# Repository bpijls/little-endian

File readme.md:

#Readme

Little-Endian is a little rover-like robot to be used for educational purposes, created by students from the Amsterdam University of Applied Sciences, (HBO-ICT, Minor IoT). The robot itself is based on a WiFi enabled microcontroller (the ESP8266) and can be programmed with a web-based blockly programming environment. For more detailed information, refer to the [design documentation](https://github.com/bpijls/little-endian/tree/master/documentation). 

**Building the robot**
The robot frame can be lasercut from 3mm mdf 
[PCB](https://dirtypcbs.com/store/designer/details/23296/6093/little-endian)

**Installation**

*	Install 'docker' and 'docker-compose' on your webserver
*	Clone this repository to a folder
*	Rename env.example to .env and determine the host name and virtual host subdomains
*	Run 'docker-compose build' from the root folder of this repository
*	To run the server, run 'docker-compose up' from the root folder
*	the server can be reached using the virtual host names you determined in the .env file or by typing the IP addres of the server in the address bar of your webbrowser. The webapplications runs on port 3000 and the socket server runs on port 8000.

**Usage**

Log in to the webapplication by entering a robot-id

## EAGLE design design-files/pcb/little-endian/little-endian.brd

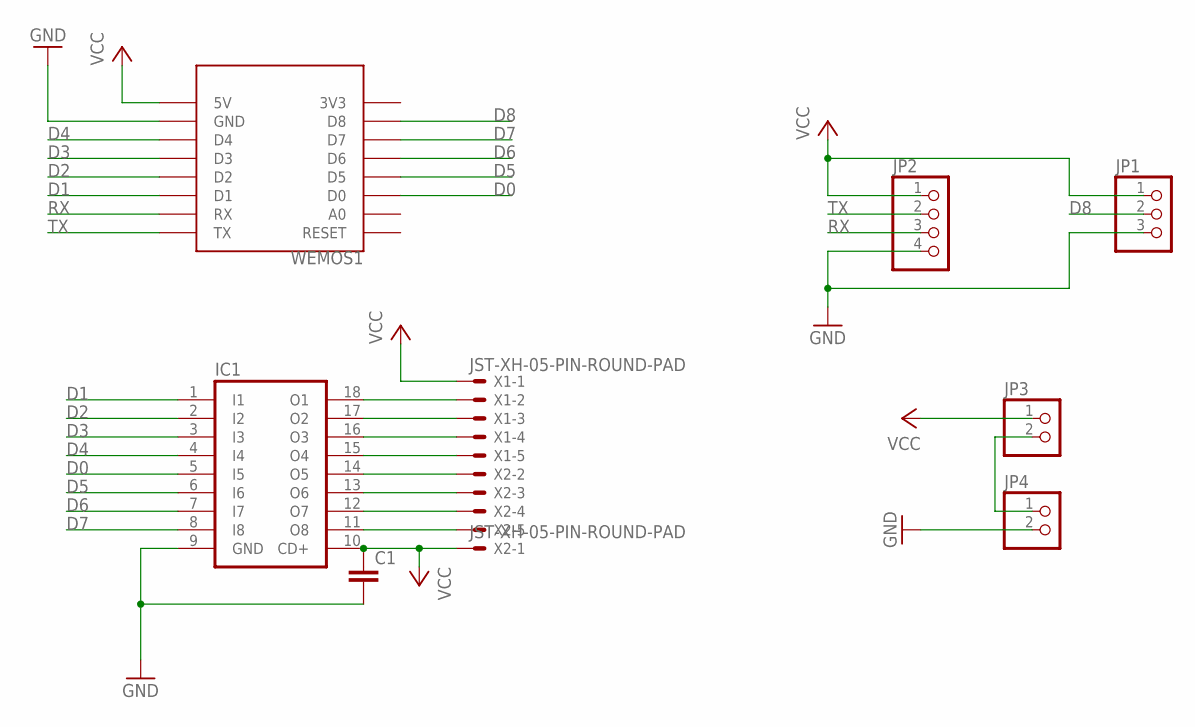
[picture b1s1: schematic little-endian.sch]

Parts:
C1: C-EU050-030X075; C050-030X075
IC1: ULN2803A; DIL18
JP1: PINHD-1X3; 1X03
JP2: PINHD-1X4; 1X04
JP3, JP4: PINHD-1X2; 1X02
WEMOS1: WEMOS-D1-MINI
X1, X2: JST-XH-05-PIN-ROUND-PAD; JST-XH-05-PACKAGE-ROUND-PAD

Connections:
D0: IC1.5 (I5), WEMOS1.D0
D1: IC1.1 (I1), WEMOS1.D1
D2: IC1.2 (I2), WEMOS1.D2
D3: IC1.3 (I3), WEMOS1.D3
D4: IC1.4 (I4), WEMOS1.D4
D5: IC1.6 (I6), WEMOS1.D5
D6: IC1.7 (I7), WEMOS1.D6
D7: IC1.8 (I8), WEMOS1.D7
D8: JP1.2, WEMOS1.D8
GND: C1.2, IC1.9 (GND), JP1.3, JP2.4, JP4.2, WEMOS1.GND
unnamed: JP3.2, JP4.1
unnamed: IC1.11 (O8), X2.5
unnamed: IC1.12 (O7), X2.4
unnamed: IC1.13 (O6), X2.3
unnamed: IC1.14 (O5), X2.2
unnamed: IC1.15 (O4), X1.5
unnamed: IC1.16 (O3), X1.4
unnamed: IC1.17 (O2), X1.3
unnamed: IC1.18 (O1), X1.2
RX: JP2.3, WEMOS1.RX
TX: JP2.2, WEMOS1.TX
VCC: C1.1, IC1.10 (CD+), JP1.1, JP2.1, JP3.1, WEMOS1.5V, X1.1, X2.1

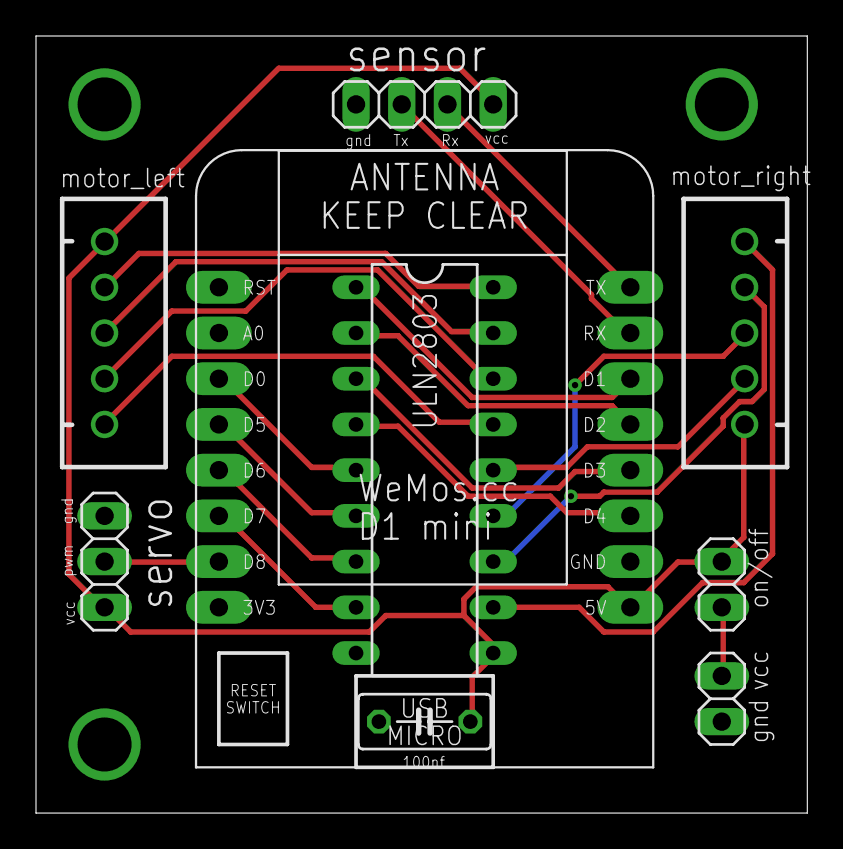
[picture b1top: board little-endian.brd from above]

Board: 2 copper layers, 42.9 x 43.2 mm, 9 parts (0 on the bottom side), 22 nets.

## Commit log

2018-07-21 Cleaned version from HvA gitlab.
2018-07-21 Updates readme.md
